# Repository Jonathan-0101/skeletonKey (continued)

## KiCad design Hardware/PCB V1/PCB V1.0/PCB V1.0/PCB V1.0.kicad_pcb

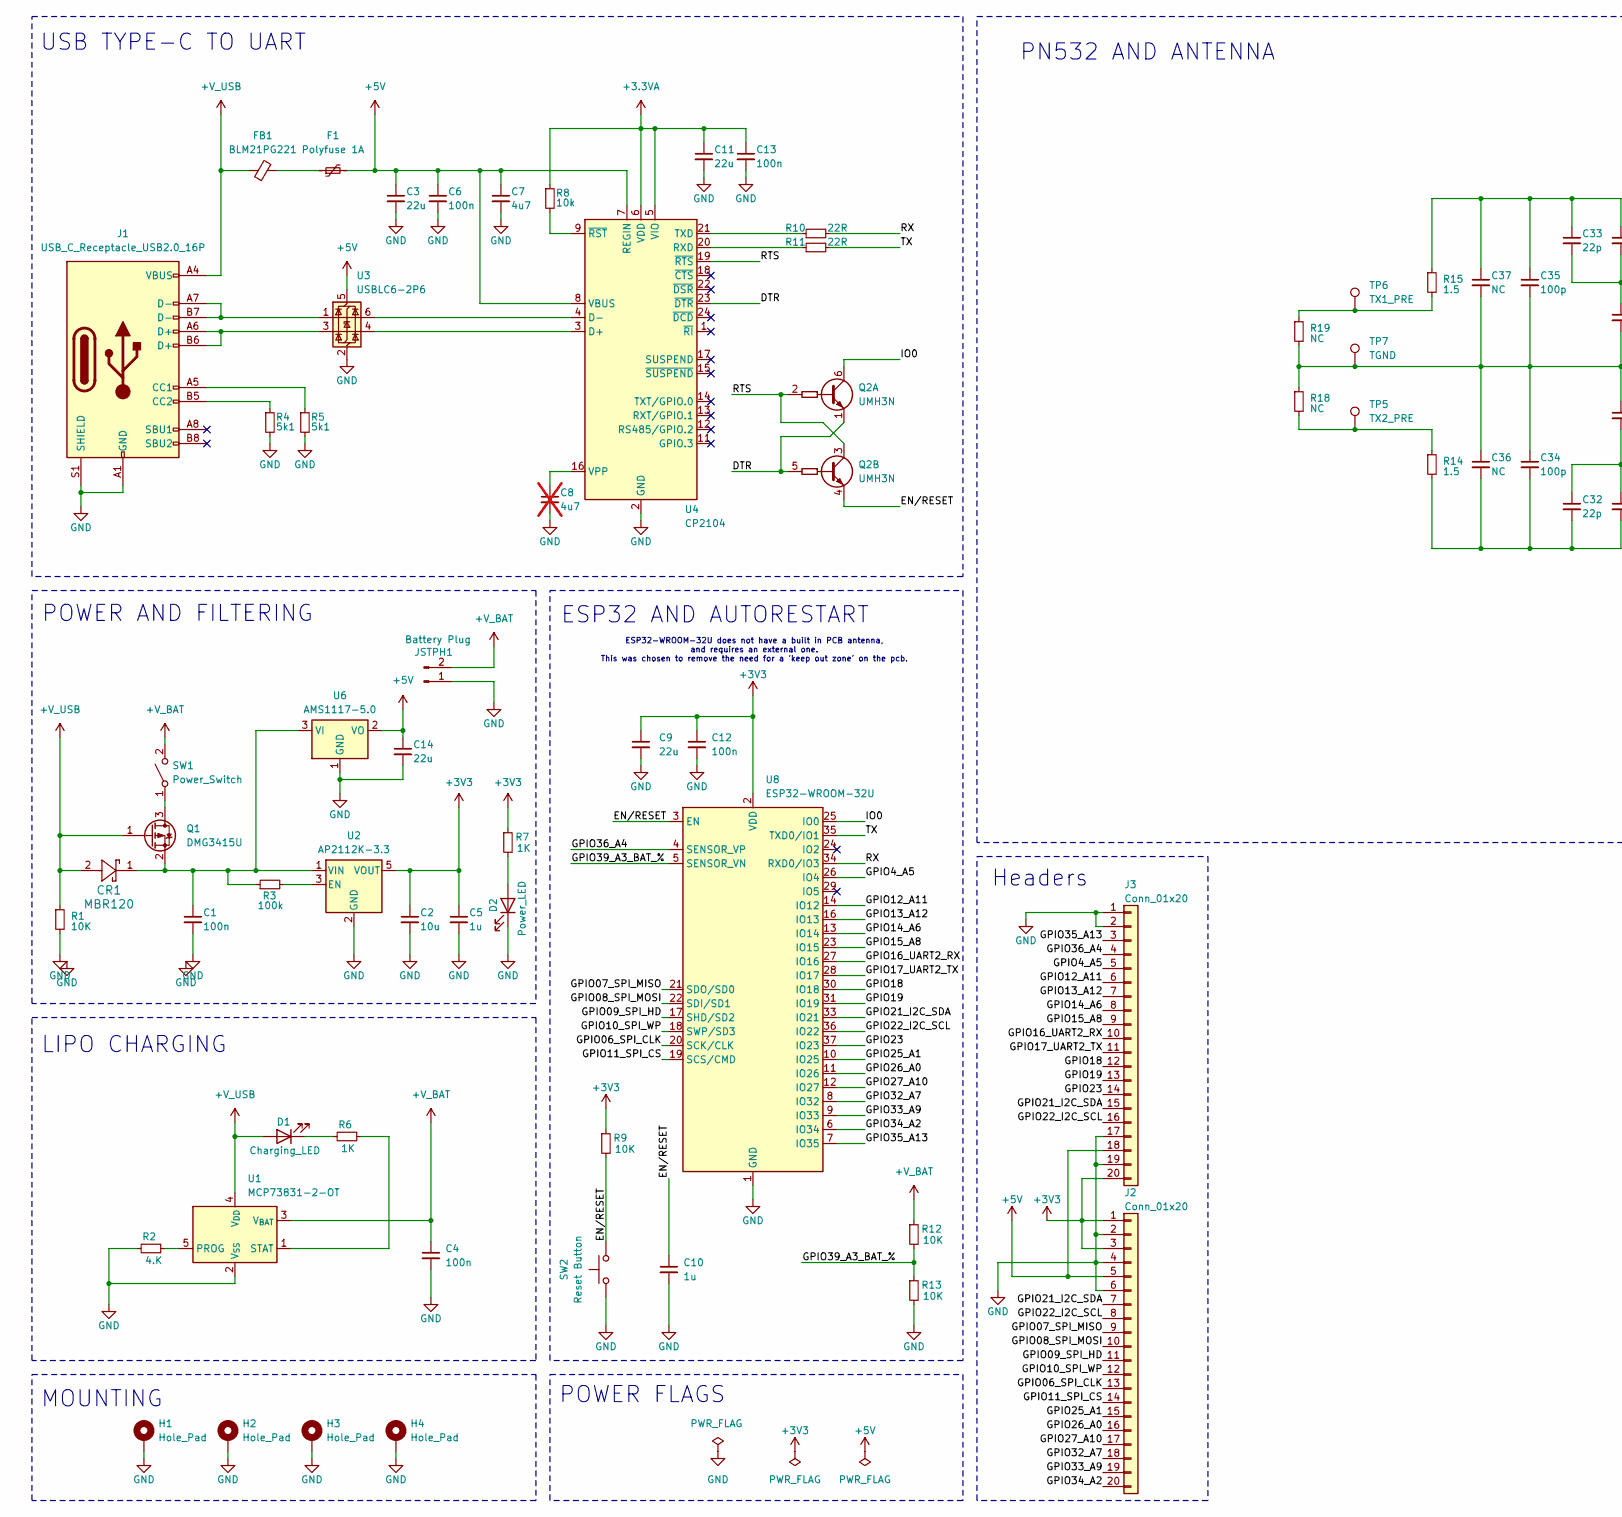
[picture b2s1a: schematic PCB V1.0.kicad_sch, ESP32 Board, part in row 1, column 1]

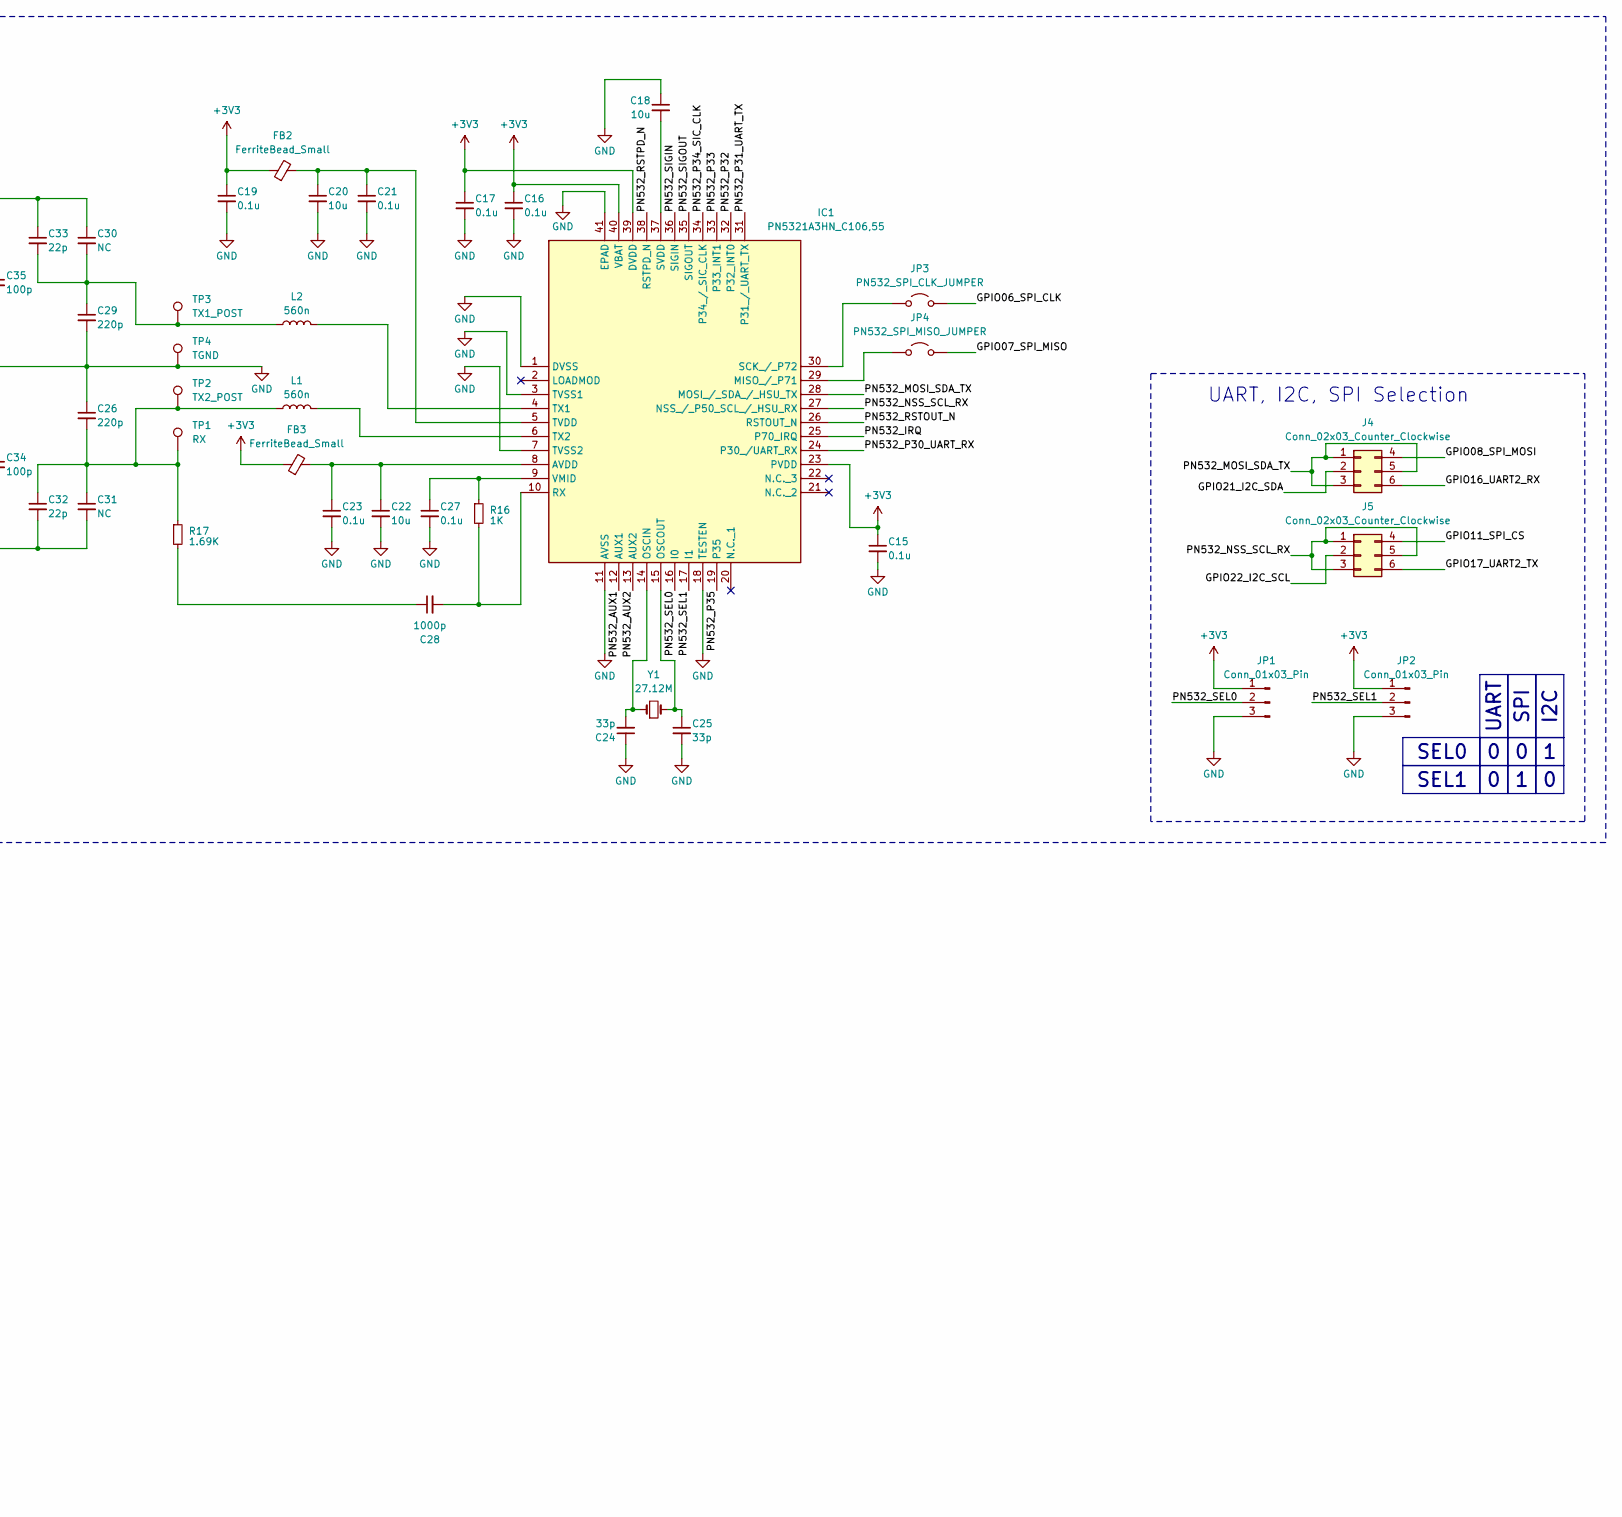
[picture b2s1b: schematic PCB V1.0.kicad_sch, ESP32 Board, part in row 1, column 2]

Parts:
C1, C6, C13: 100n; C_0805_2012Metric_Pad1.18x1.45mm_HandSolder
C2: 10u; C_0805_2012Metric_Pad1.18x1.45mm_HandSolder
C3, C9, C11: 22u; C_0805_2012Metric_Pad1.18x1.45mm_HandSolder
C4, C12: 100n; C_0402_1005Metric_Pad0.74x0.62mm_HandSolder
C5: 1u; C_0805_2012Metric_Pad1.18x1.45mm_HandSolder
C7: 4u7; C_0805_2012Metric_Pad1.18x1.45mm_HandSolder
C8: 4u7; C_0805_2012Metric_Pad1.18x1.45mm_HandSolder; not fitted
C10: 1u; C_0402_1005Metric_Pad0.74x0.62mm_HandSolder
C14: 22u; C_Axial_L3.8mm_D2.6mm_P10.00mm_Horizontal
C15, C16, C17, C19, C21, C23, C27: 0.1u; C_Axial_L3.8mm_D2.6mm_P10.00mm_Horizontal
C18, C20, C22: 10u; C_Axial_L3.8mm_D2.6mm_P10.00mm_Horizontal
C24, C25: 33p; C_Axial_L3.8mm_D2.6mm_P10.00mm_Horizontal
C26, C29: 220p; C_Axial_L3.8mm_D2.6mm_P10.00mm_Horizontal
C28: 1000p; C_Axial_L3.8mm_D2.6mm_P10.00mm_Horizontal
C30, C31, C36, C37: NC; C_Axial_L3.8mm_D2.6mm_P10.00mm_Horizontal
C32, C33: 22p; C_Axial_L3.8mm_D2.6mm_P10.00mm_Horizontal
C34, C35: 100p; C_Axial_L3.8mm_D2.6mm_P10.00mm_Horizontal
CR1: MBR120; SDO_SOD-123FL498_OSI
D1: Charging_LED; LED_0603_1608Metric_Pad1.05x0.95mm_HandSolder
D2: Power_LED; LED_0603_1608Metric_Pad1.05x0.95mm_HandSolder
F1: Polyfuse 1A; Fuse_1206_3216Metric_Pad1.42x1.75mm_HandSolder
FB1: BLM21PG221; L_0603_1608Metric_Pad1.05x0.95mm_HandSolder
FB2, FB3: FerriteBead_Small; BEADC2012X145N
H1, H2, H3, H4: Hole_Pad; MountingHole_2.2mm_M2_Pad_Via
IC1: PN5321A3HN_C106,55; QFN50P600X600X100-41N-D; Mouser Part Number 771-PN5321A3HNC10
J1: USB_C_Receptacle_USB2.0_16P; USB_C_Receptacle_HRO_TYPE-C-31-M-12
J2, J3: Conn_01x20; PinSocket_1x20_P2.54mm_Vertical
J4, J5: Conn_02x03_Counter_Clockwise; PinHeader_2x03_P2.54mm_Vertical
JP1, JP2: Conn_01x03_Pin; PinHeader_1x03_P2.54mm_Vertical
JP3: PN532_SPI_CLK_JUMPER; TestPoint_2Pads_Pitch5.08mm_Drill1.3mm
JP4: PN532_SPI_MISO_JUMPER; TestPoint_2Pads_Pitch5.08mm_Drill1.3mm
JSTPH1: Battery Plug; JST_PH_S2B-PH-K_1x02_P2.00mm_Horizontal
L1, L2: 560n; L_Axial_L5.3mm_D2.2mm_P10.16mm_Horizontal_Vishay_IM-1
Q1: DMG3415U; SOT95P240X105-3N
Q2: UMH3N; SOT-363_SC-70-6
R1, R9, R12, R13: 10K; R_0402_1005Metric_Pad0.72x0.64mm_HandSolder
R2: 4.K; R_0402_1005Metric_Pad0.72x0.64mm_HandSolder
R3: 100k; R_0402_1005Metric_Pad0.72x0.64mm_HandSolder
R4, R5: 5k1; R_0402_1005Metric_Pad0.72x0.64mm_HandSolder
R6, R7: 1K; R_0402_1005Metric_Pad0.72x0.64mm_HandSolder
R8: 10k; R_0402_1005Metric_Pad0.72x0.64mm_HandSolder
R10, R11: 22R; R_0402_1005Metric_Pad0.72x0.64mm_HandSolder
R14, R15: 1.5; R_Axial_DIN0207_L6.3mm_D2.5mm_P10.16mm_Horizontal
R16: 1K; R_Axial_DIN0207_L6.3mm_D2.5mm_P10.16mm_Horizontal
R17: 1.69K; R_Axial_DIN0207_L6.3mm_D2.5mm_P10.16mm_Horizontal
R18, R19: NC; R_Axial_DIN0207_L6.3mm_D2.5mm_P10.16mm_Horizontal
SW1: Power_Switch; SW_DIP_SPSTx01_Slide_9.78x4.72mm_W7.62mm_P2.54mm
SW2: Reset Button; SW_Push_SPST_NO_Alps_SKRK
TP1: RX; TestPoint_Pad_D1.5mm
TP2: TX2_POST; TestPoint_Pad_D1.5mm
TP3: TX1_POST; TestPoint_Pad_D1.5mm
TP4, TP7: TGND; TestPoint_Pad_D1.5mm
TP5: TX2_PRE; TestPoint_Pad_D1.5mm
TP6: TX1_PRE; TestPoint_Pad_D1.5mm
U1: MCP73831-2-OT; SOT-23-5
U2: AP2112K-3.3; SOT-23-5
U3: USBLC6-2P6; SOT-666
U4: CP2104; QFN-24-1EP_4x4mm_P0.5mm_EP2.6x2.6mm
U6: AMS1117-5.0; SOT-223-3_TabPin2
U8: ESP32-WROOM-32U
Y1: 27.12M; XTAL_7M-27.120MAAJ-T

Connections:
+3.3VA: C11.1, C13.1, R8.1, U4.5 (VIO), U4.6 (VDD)
+3V3: C2.1, C5.1, C9.1, C12.1, C15.1, C16.1, C17.1, C19.1, FB2.1, FB3.1, IC1.23 (PVDD), IC1.39 (DVDD), IC1.40 (VBAT), J2.1, J2.3, J3.20, JP1.1, JP2.1, R7.1, R9.1, U2.5 (VOUT), U8.2 (VDD)
+5V: C3.1, C6.1, C7.1, C14.1, F1.2, J2.5, J3.18, U3.5 (VBUS), U4.7 (REGIN), U4.8 (VBUS), U6.2 (VO)
+V_BAT: C4.1, JSTPH1.2, R12.1, SW1.2 (B), U1.3 (V_{BAT})
+V_USB: CR1.2, D1.2 (A), FB1.1, J1.A4 (VBUS), J1.A9 (VBUS), J1.B4 (VBUS), J1.B9 (VBUS), Q1.1 (G), R1.1, U1.4 (V_{DD})
/DTR: Q2.1 (E1), Q2.5 (B2), U4.23 (~DTR)
/EN/RESET: C10.1, Q2.4 (E2), R9.2, SW2.2, U8.3 (EN)
/GPIO4_A5: J3.5, U8.26 (IO4)
/GPIO06_SPI_CLK: J2.13, JP3.2 (B), U8.20 (SCK/CLK)
/GPIO07_SPI_MISO: J2.9, JP4.2 (B), U8.21 (SDO/SD0)
/GPIO08_SPI_MOSI: J2.10, J4.4, U8.22 (SDI/SD1)
/GPIO09_SPI_HD: J2.11, U8.17 (SHD/SD2)
/GPIO10_SPI_WP: J2.12, U8.18 (SWP/SD3)
/GPIO11_SPI_CS: J2.14, J5.4, U8.19 (SCS/CMD)
/GPIO12_A11: J3.6, U8.14 (IO12)
/GPIO13_A12: J3.7, U8.16 (IO13)
/GPIO14_A6: J3.8, U8.13 (IO14)
/GPIO15_A8: J3.9, U8.23 (IO15)
/GPIO16_UART2_RX: J3.10, J4.6, U8.27 (IO16)
/GPIO17_UART2_TX: J3.11, J5.6, U8.28 (IO17)
/GPIO18: J3.12, U8.30 (IO18)
/GPIO19: J3.13, U8.31 (IO19)
/GPIO21_I2C_SDA: J2.7, J3.15, J4.2, U8.33 (IO21)
/GPIO22_I2C_SCL: J2.8, J3.16, J5.2, U8.36 (IO22)
/GPIO23: J3.14, U8.37 (IO23)
/GPIO25_A1: J2.15, U8.10 (IO25)
/GPIO26_A0: J2.16, U8.11 (IO26)
/GPIO27_A10: J2.17, U8.12 (IO27)
/GPIO32_A7: J2.18, U8.8 (IO32)
/GPIO33_A9: J2.19, U8.9 (IO33)
/GPIO34_A2: J2.20, U8.6 (IO34)
/GPIO35_A13: J3.3, U8.7 (IO35)
/GPIO36_A4: J3.4, U8.4 (SENSOR_VP)
/GPIO39_A3_BAT_%: R12.2, R13.1, U8.5 (SENSOR_VN)
/IO0: Q2.6 (C1), U8.25 (IO0)
/PN532_AUX1: IC1.12 (AUX1)
/PN532_AUX2: IC1.13 (AUX2)
/PN532_IRQ: IC1.25 (P70_IRQ)
/PN532_MOSI_SDA_TX: IC1.28 (MOSI_/_SDA_/_HSU_TX), J4.1, J4.3, J4.5
/PN532_NSS_SCL_RX: IC1.27 (NSS_/_P50_SCL_/_HSU_RX), J5.1, J5.3, J5.5
/PN532_P30_UART_RX: IC1.24 (P30_/UART_RX)
/PN532_P31_UART_TX: IC1.31 (P31_/_UART_TX)
/PN532_P32: IC1.32 (P32_INT0)
/PN532_P33: IC1.33 (P33_INT1)
/PN532_P34_SIC_CLK: IC1.34 (P34_/_SIC_CLK)
/PN532_P35: IC1.19 (P35)
/PN532_RSTOUT_N: IC1.26 (RSTOUT_N)
/PN532_RSTPD_N: IC1.38 (RSTPD_N)
/PN532_SEL0: IC1.16 (I0), JP1.2
/PN532_SEL1: IC1.17 (I1), JP2.2
/PN532_SIGIN: IC1.36 (SIGIN)
/PN532_SIGOUT: IC1.35 (SIGOUT)
/RTS: Q2.2 (B1), Q2.3 (C2), U4.19 (~RTS)
/RX: R10.2, U8.34 (RXD0/IO3)
/TX: R11.2, U8.35 (TXD0/IO1)
GND: C1.2, C2.2, C3.2, C4.2, C5.2, C6.2, C7.2, C8.2, C9.2, C10.2, C11.2, C12.2, C13.2, C14.2, C15.2, C16.2, C17.2, C18.1, C19.2, C20.2, C21.2, C22.2, C23.2, C24.1, C25.2, C26.1, C27.2, C29.2, C34.1, C35.2, C36.1, C37.2, D2.1 (K), H1.1, H2.1, H3.1, H4.1, IC1.1 (DVSS), IC1.3 (TVSS1), IC1.7 (TVSS2), IC1.11 (AVSS), IC1.18 (TESTEN), IC1.41 (EPAD), J1.A1 (GND), J1.A12 (GND), J1.B1 (GND), J1.B12 (GND), J1.S1 (SHIELD), J2.2, J2.4, J2.6, J3.1, J3.2, J3.17, J3.19, JP1.3, JP2.3, JSTPH1.1, R1.2, R2.2, R4.2, R5.2, R13.2, R18.1, R19.2, SW2.1, TP4.1, TP7.1, U1.2 (V_{SS}), U2.2 (GND), U3.2 (GND), U4.2 (GND), U4.25 (GND), U6.1 (GND), U8.1 (GND), U8.15 (GND), U8.38 (GND), U8.39 (GND)
unnamed: C26.2, C31.1, C32.1, L1.1, R17.1, TP1.1, TP2.1
unnamed: C28.1, R17.2
unnamed: C29.1, C30.2, C33.2, L2.1, TP3.1
unnamed: C30.1, C33.1, C35.1, C37.1, R15.1
unnamed: C31.2, C32.2, C34.2, C36.2, R14.2
unnamed: D1.1 (K), R6.2
unnamed: D2.2 (A), R7.2
unnamed: F1.1, FB1.2
unnamed: C22.1, C23.1, FB3.2, IC1.8 (AVDD)
unnamed: IC1.29 (MISO_/_P71), JP4.1 (A)
unnamed: C24.2, IC1.14 (OSCIN), Y1.1
unnamed: C25.1, IC1.15 (OSCOUT), Y1.2
unnamed: C28.2, IC1.10 (RX), R16.2
unnamed: IC1.30 (SCK_/_P72), JP3.1 (A)
unnamed: C18.2, IC1.37 (SVDD)
unnamed: C20.1, C21.1, FB2.2, IC1.5 (TVDD)
unnamed: IC1.4 (TX1), L2.2
unnamed: IC1.6 (TX2), L1.2
unnamed: C27.1, IC1.9 (VMID), R16.1
unnamed: J1.A5 (CC1), R5.1
unnamed: J1.B5 (CC2), R4.1
unnamed: J1.A6 (D+), J1.B6 (D+), U3.3 (I/O2)
unnamed: J1.A7 (D-), J1.B7 (D-), U3.1 (I/O1)
unnamed: Q1.3 (D), SW1.1 (A)
unnamed: C1.1, CR1.1, Q1.2 (S), R3.1, U2.1 (VIN), U6.3 (VI)
unnamed: R14.1, R18.2, TP5.1
unnamed: R15.2, R19.1, TP6.1
unnamed: R2.1, U1.5 (PROG)
unnamed: R6.1, U1.1 (STAT)
unnamed: R3.2, U2.3 (EN)
unnamed: U3.4 (I/O2), U4.3 (D+)
unnamed: U3.6 (I/O1), U4.4 (D-)
unnamed: R11.1, U4.20 (RXD)
unnamed: R10.1, U4.21 (TXD)
unnamed: C8.1, U4.16 (VPP)
unnamed: R8.2, U4.9 (~RST)

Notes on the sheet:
SPI
I2C
SEL0
UART
SEL1
PN532 AND ANTENNA
LIPO CHARGING
Headers
ESP32-WROOM-32U does not have a built in PCB antenna, and requires an external one. This was chosen to remove the need for a 'keep out zone' on the pcb.
USB TYPE-C TO UART
ESP32 AND AUTORESTART
UART, I2C, SPI Selection
POWER FLAGS
MOUNTING
POWER AND FILTERING

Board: 2 copper layers, 97 parts (0 on the bottom side), 78 nets, no tracks yet.

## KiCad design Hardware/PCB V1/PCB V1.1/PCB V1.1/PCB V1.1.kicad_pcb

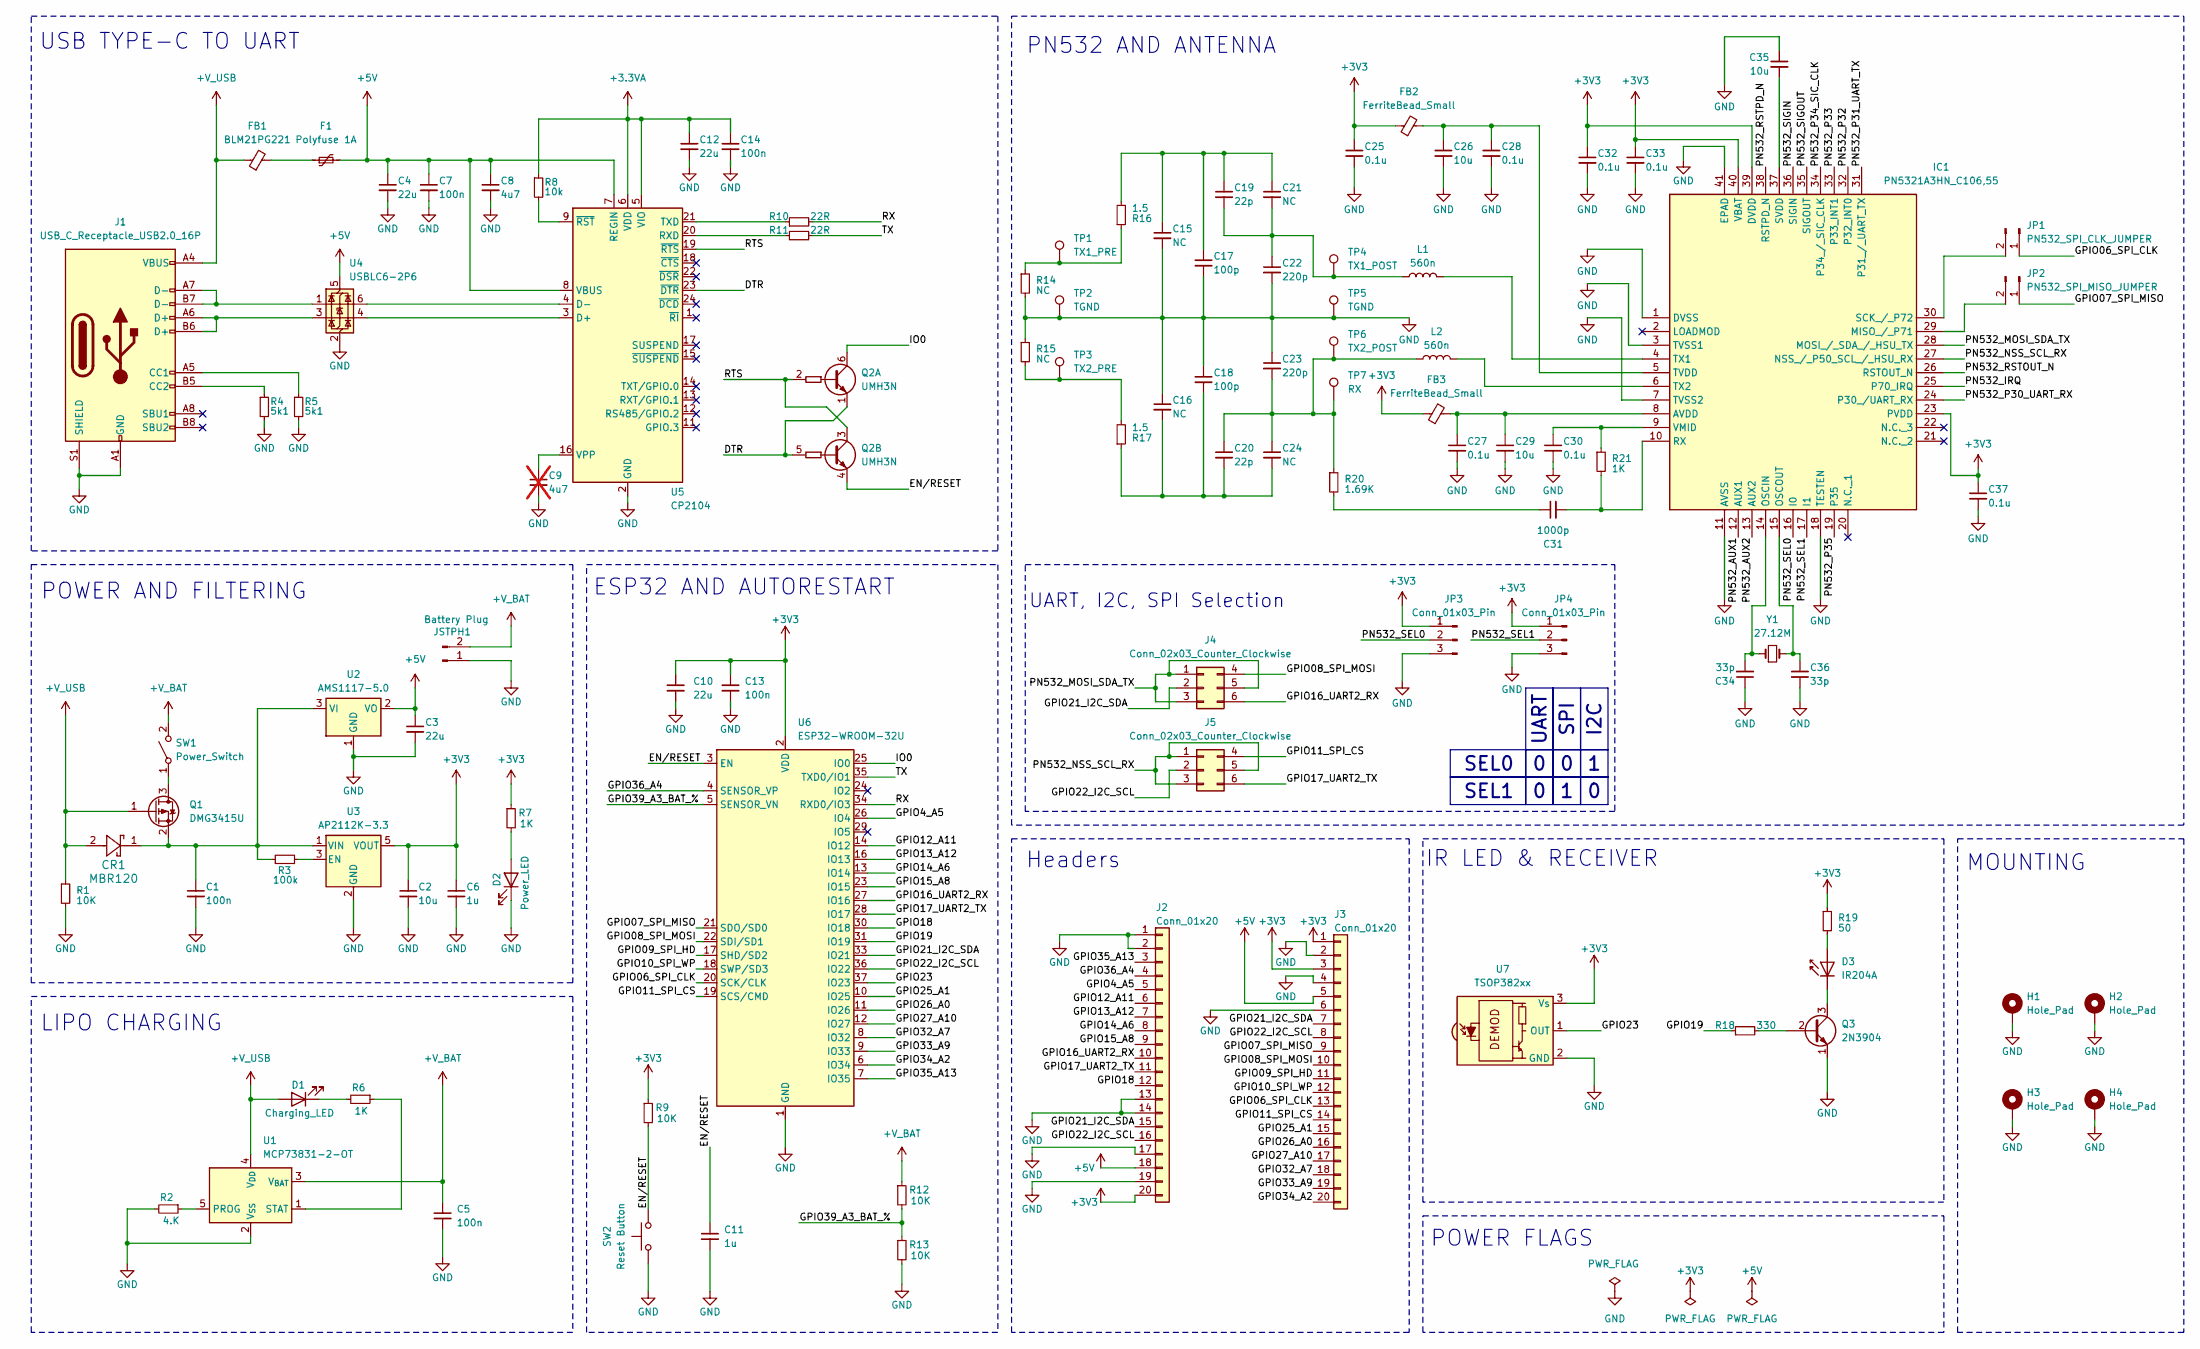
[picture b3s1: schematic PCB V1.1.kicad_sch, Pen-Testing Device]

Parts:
C1, C7, C14: 100n; C_0805_2012Metric_Pad1.18x1.45mm_HandSolder
C2: 10u; C_0805_2012Metric_Pad1.18x1.45mm_HandSolder
C3, C4, C10, C12: 22u; C_0805_2012Metric_Pad1.18x1.45mm_HandSolder
C5, C13: 100n; C_0402_1005Metric_Pad0.74x0.62mm_HandSolder
C6: 1u; C_0805_2012Metric_Pad1.18x1.45mm_HandSolder
C8: 4u7; C_0805_2012Metric_Pad1.18x1.45mm_HandSolder
C9: 4u7; C_0805_2012Metric_Pad1.18x1.45mm_HandSolder; not fitted
C11: 1u; C_0402_1005Metric_Pad0.74x0.62mm_HandSolder
C15, C16, C21, C24: NC; C_Disc_D7.5mm_W2.5mm_P5.00mm
C17, C18: 100p; C_Disc_D7.5mm_W2.5mm_P5.00mm
C19, C20: 22p; C_Disc_D7.5mm_W2.5mm_P5.00mm
C22, C23: 220p; C_Disc_D7.5mm_W2.5mm_P5.00mm
C25, C27, C28, C30, C32, C33, C37: 0.1u; C_Disc_D7.5mm_W2.5mm_P5.00mm
C26, C29, C35: 10u; C_Disc_D7.5mm_W2.5mm_P5.00mm
C31: 1000p; C_Disc_D7.5mm_W2.5mm_P5.00mm
C34, C36: 33p; C_Disc_D7.5mm_W2.5mm_P5.00mm
CR1: MBR120; SDO_SOD-123FL498_OSI
D1: Charging_LED; LED_0603_1608Metric_Pad1.05x0.95mm_HandSolder
D2: Power_LED; LED_0603_1608Metric_Pad1.05x0.95mm_HandSolder
D3: IR204A; LED_D3.0mm_IRBlack
F1: Polyfuse 1A; Fuse_1206_3216Metric_Pad1.42x1.75mm_HandSolder
FB1: BLM21PG221; L_0603_1608Metric_Pad1.05x0.95mm_HandSolder
FB2, FB3: FerriteBead_Small; BEADC2012X145N
H1, H2, H3, H4: Hole_Pad; MountingHole_2.2mm_M2_Pad_Via
IC1: PN5321A3HN_C106,55; QFN50P600X600X100-41N-D; Mouser Part Number 771-PN5321A3HNC10
J1: USB_C_Receptacle_USB2.0_16P; USB_C_Receptacle_HRO_TYPE-C-31-M-12
J2, J3: Conn_01x20; PinSocket_1x20_P2.54mm_Vertical
J4, J5: Conn_02x03_Counter_Clockwise; PinHeader_2x03_P2.54mm_Vertical
JP1: PN532_SPI_CLK_JUMPER; PinHeader_2x01_P2.54mm_Vertical
JP2: PN532_SPI_MISO_JUMPER; PinHeader_2x01_P2.54mm_Vertical
JP3, JP4: Conn_01x03_Pin; PinHeader_1x03_P2.54mm_Vertical
JSTPH1: Battery Plug; JST_PH_S2B-PH-K_1x02_P2.00mm_Horizontal
L1, L2: 560n; L_Axial_L5.3mm_D2.2mm_P10.16mm_Horizontal_Vishay_IM-1
Q1: DMG3415U; SOT95P240X105-3N
Q2: UMH3N; SOT-363_SC-70-6
Q3: 2N3904; TO-92_Inline
R1, R9, R12, R13: 10K; R_0402_1005Metric_Pad0.72x0.64mm_HandSolder
R2: 4.K; R_0402_1005Metric_Pad0.72x0.64mm_HandSolder
R3: 100k; R_0402_1005Metric_Pad0.72x0.64mm_HandSolder
R4, R5: 5k1; R_0402_1005Metric_Pad0.72x0.64mm_HandSolder
R6, R7: 1K; R_0402_1005Metric_Pad0.72x0.64mm_HandSolder
R8: 10k; R_0402_1005Metric_Pad0.72x0.64mm_HandSolder
R10, R11: 22R; R_0402_1005Metric_Pad0.72x0.64mm_HandSolder
R14, R15: NC; R_0201_0603Metric_Pad0.64x0.40mm_HandSolder
R16, R17: 1.5; R_Axial_DIN0207_L6.3mm_D2.5mm_P10.16mm_Horizontal
R18: 330; R_Axial_DIN0207_L6.3mm_D2.5mm_P10.16mm_Horizontal
R19: 50; R_Axial_DIN0207_L6.3mm_D2.5mm_P10.16mm_Horizontal
R20: 1.69K; R_Axial_DIN0207_L6.3mm_D2.5mm_P10.16mm_Horizontal
R21: 1K; R_Axial_DIN0207_L6.3mm_D2.5mm_P10.16mm_Horizontal
SW1: Power_Switch; SW_DIP_SPSTx01_Slide_9.78x4.72mm_W7.62mm_P2.54mm
SW2: Reset Button; SW_Push_SPST_NO_Alps_SKRK
TP1: TX1_PRE; TestPoint_Pad_D1.5mm
TP2, TP5: TGND; TestPoint_Pad_D1.5mm
TP3: TX2_PRE; TestPoint_Pad_D1.5mm
TP4: TX1_POST; TestPoint_Pad_D1.5mm
TP6: TX2_POST; TestPoint_Pad_D1.5mm
TP7: RX; TestPoint_Pad_D1.5mm
U1: MCP73831-2-OT; SOT-23-5
U2: AMS1117-5.0; SOT-223-3_TabPin2
U3: AP2112K-3.3; SOT-23-5
U4: USBLC6-2P6; SOT-666
U5: CP2104; QFN-24-1EP_4x4mm_P0.5mm_EP2.6x2.6mm
U6: ESP32-WROOM-32U
U7: TSOP382xx; Vishay_MINICAST-3Pin
Y1: 27.12M; XTAL_7M-27.120MAAJ-T

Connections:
+3.3VA: C12.1, C14.1, R8.1, U5.5 (VIO), U5.6 (VDD)
+V_BAT: C5.1, JSTPH1.2, R12.1, SW1.2 (B), U1.3 (V_{BAT})
+V_USB: CR1.2, D1.2 (A), FB1.1, J1.A4 (VBUS), J1.A9 (VBUS), J1.B4 (VBUS), J1.B9 (VBUS), Q1.1 (G), R1.1, U1.4 (V_{DD})
/DTR: Q2.1 (E1), Q2.5 (B2), U5.23 (~DTR)
/EN/RESET: C11.1, Q2.4 (E2), R9.2, SW2.2, U6.3 (EN)
/GPIO4_A5: J2.5, U6.26 (IO4)
/GPIO06_SPI_CLK: J3.13, JP1.1, U6.20 (SCK/CLK)
/GPIO07_SPI_MISO: J3.9, JP2.1, U6.21 (SDO/SD0)
/GPIO08_SPI_MOSI: J3.10, J4.4, U6.22 (SDI/SD1)
/GPIO09_SPI_HD: J3.11, U6.17 (SHD/SD2)
/GPIO10_SPI_WP: J3.12, U6.18 (SWP/SD3)
/GPIO11_SPI_CS: J3.14, J5.4, U6.19 (SCS/CMD)
/GPIO12_A11: J2.6, U6.14 (IO12)
/GPIO13_A12: J2.7, U6.16 (IO13)
/GPIO14_A6: J2.8, U6.13 (IO14)
/GPIO15_A8: J2.9, U6.23 (IO15)
/GPIO16_UART2_RX: J2.10, J4.6, U6.27 (IO16)
/GPIO17_UART2_TX: J2.11, J5.6, U6.28 (IO17)
/GPIO18: J2.12, U6.30 (IO18)
/GPIO19: R18.1, U6.31 (IO19)
/GPIO21_I2C_SDA: J2.15, J3.7, J4.2, U6.33 (IO21)
/GPIO22_I2C_SCL: J2.16, J3.8, J5.2, U6.36 (IO22)
/GPIO23: U6.37 (IO23), U7.1 (OUT)
/GPIO25_A1: J3.15, U6.10 (IO25)
/GPIO26_A0: J3.16, U6.11 (IO26)
/GPIO27_A10: J3.17, U6.12 (IO27)
/GPIO32_A7: J3.18, U6.8 (IO32)
/GPIO33_A9: J3.19, U6.9 (IO33)
/GPIO34_A2: J3.20, U6.6 (IO34)
/GPIO35_A13: J2.3, U6.7 (IO35)
/GPIO36_A4: J2.4, U6.4 (SENSOR_VP)
/GPIO39_A3_BAT_%: R12.2, R13.1, U6.5 (SENSOR_VN)
/IO0: Q2.6 (C1), U6.25 (IO0)
/PN532_AUX1: IC1.12 (AUX1)
/PN532_AUX2: IC1.13 (AUX2)
/PN532_IRQ: IC1.25 (P70_IRQ)
/PN532_MOSI_SDA_TX: IC1.28 (MOSI_/_SDA_/_HSU_TX), J4.1, J4.3, J4.5
/PN532_NSS_SCL_RX: IC1.27 (NSS_/_P50_SCL_/_HSU_RX), J5.1, J5.3, J5.5
/PN532_P30_UART_RX: IC1.24 (P30_/UART_RX)
/PN532_P31_UART_TX: IC1.31 (P31_/_UART_TX)
/PN532_P32: IC1.32 (P32_INT0)
/PN532_P33: IC1.33 (P33_INT1)
/PN532_P34_SIC_CLK: IC1.34 (P34_/_SIC_CLK)
/PN532_P35: IC1.19 (P35)
/PN532_RSTOUT_N: IC1.26 (RSTOUT_N)
/PN532_RSTPD_N: IC1.38 (RSTPD_N)
/PN532_SEL0: IC1.16 (I0), JP3.2
/PN532_SEL1: IC1.17 (I1), JP4.2
/PN532_SIGIN: IC1.36 (SIGIN)
/PN532_SIGOUT: IC1.35 (SIGOUT)
/RTS: Q2.2 (B1), Q2.3 (C2), U5.19 (~RTS)
/RX: R10.2, U6.34 (RXD0/IO3)
/TX: R11.2, U6.35 (TXD0/IO1)
GND: C1.2, C2.2, C3.2, C4.2, C5.2, C6.2, C7.2, C8.2, C9.2, C10.2, C11.2, C12.2, C13.2, C14.2, C15.2, C16.1, C17.2, C18.1, C22.2, C23.1, C25.2, C26.2, C27.2, C28.2, C29.2, C30.2, C32.2, C33.2, C34.1, C35.1, C36.2, C37.2, D2.1 (K), H1.1, H2.1, H3.1, H4.1, IC1.1 (DVSS), IC1.3 (TVSS1), IC1.7 (TVSS2), IC1.11 (AVSS), IC1.18 (TESTEN), IC1.41 (EPAD), J1.A1 (GND), J1.A12 (GND), J1.B1 (GND), J1.B12 (GND), J1.S1 (SHIELD), J2.1, J2.2, J2.13, J2.14, J2.17, J2.19, J3.2, J3.4, J3.6, JP3.3, JP4.3, JSTPH1.1, Q3.1 (E), R1.2, R2.2, R4.2, R5.2, R13.2, R14.2, R15.1, SW2.1, TP2.1, TP5.1, U1.2 (V_{SS}), U2.1 (GND), U3.2 (GND), U4.2 (GND), U5.2 (GND), U5.25 (GND), U6.1 (GND), U6.15 (GND), U6.38 (GND), U6.39 (GND), U7.2 (GND); also elsewhere on the board
unnamed: C15.1, C17.1, C19.1, C21.1, R16.2
unnamed: C16.2, C18.2, C20.2, C24.2, R17.1
unnamed: C19.2, C21.2, C22.1, L1.1, TP4.1
unnamed: C20.1, C23.2, C24.1, L2.1, R20.1, TP6.1, TP7.1
unnamed: C31.1, R20.2
unnamed: D1.1 (K), R6.2
unnamed: D2.2 (A), R7.2
unnamed: D3.2 (A), R19.2
unnamed: D3.1 (K), Q3.3 (C)
unnamed: F1.1, FB1.2
unnamed: C27.1, C29.1, FB3.2, IC1.8 (AVDD)
unnamed: IC1.29 (MISO_/_P71), JP2.2
unnamed: C34.2, IC1.14 (OSCIN), Y1.1
unnamed: C36.1, IC1.15 (OSCOUT), Y1.2
unnamed: C31.2, IC1.10 (RX), R21.2
unnamed: IC1.30 (SCK_/_P72), JP1.2
unnamed: C35.2, IC1.37 (SVDD)
unnamed: C26.1, C28.1, FB2.2, IC1.5 (TVDD)
unnamed: IC1.4 (TX1), L1.2
unnamed: IC1.6 (TX2), L2.2
unnamed: C30.1, IC1.9 (VMID), R21.1
unnamed: J1.A5 (CC1), R5.1
unnamed: J1.B5 (CC2), R4.1
unnamed: J1.A6 (D+), J1.B6 (D+), U4.3 (I/O2)
unnamed: J1.A7 (D-), J1.B7 (D-), U4.1 (I/O1)
unnamed: Q1.3 (D), SW1.1 (A)
unnamed: C1.1, CR1.1, Q1.2 (S), R3.1, U2.3 (VI), U3.1 (VIN)
unnamed: Q3.2 (B), R18.2
unnamed: R14.1, R16.1, TP1.1
unnamed: R15.2, R17.2, TP3.1
unnamed: R2.1, U1.5 (PROG)
unnamed: R6.1, U1.1 (STAT)
unnamed: R3.2, U3.3 (EN)
unnamed: U4.4 (I/O2), U5.3 (D+)
unnamed: U4.6 (I/O1), U5.4 (D-)
unnamed: R11.1, U5.20 (RXD)
unnamed: R10.1, U5.21 (TXD)
unnamed: C9.1, U5.16 (VPP)
unnamed: R8.2, U5.9 (~RST)

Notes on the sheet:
I2C
UART
SPI
SEL0
SEL1
LIPO CHARGING
IR LED & RECEIVER
UART, I2C, SPI Selection
Headers
USB TYPE-C TO UART
PN532 AND ANTENNA
ESP32 AND AUTORESTART
POWER FLAGS
MOUNTING
POWER AND FILTERING

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
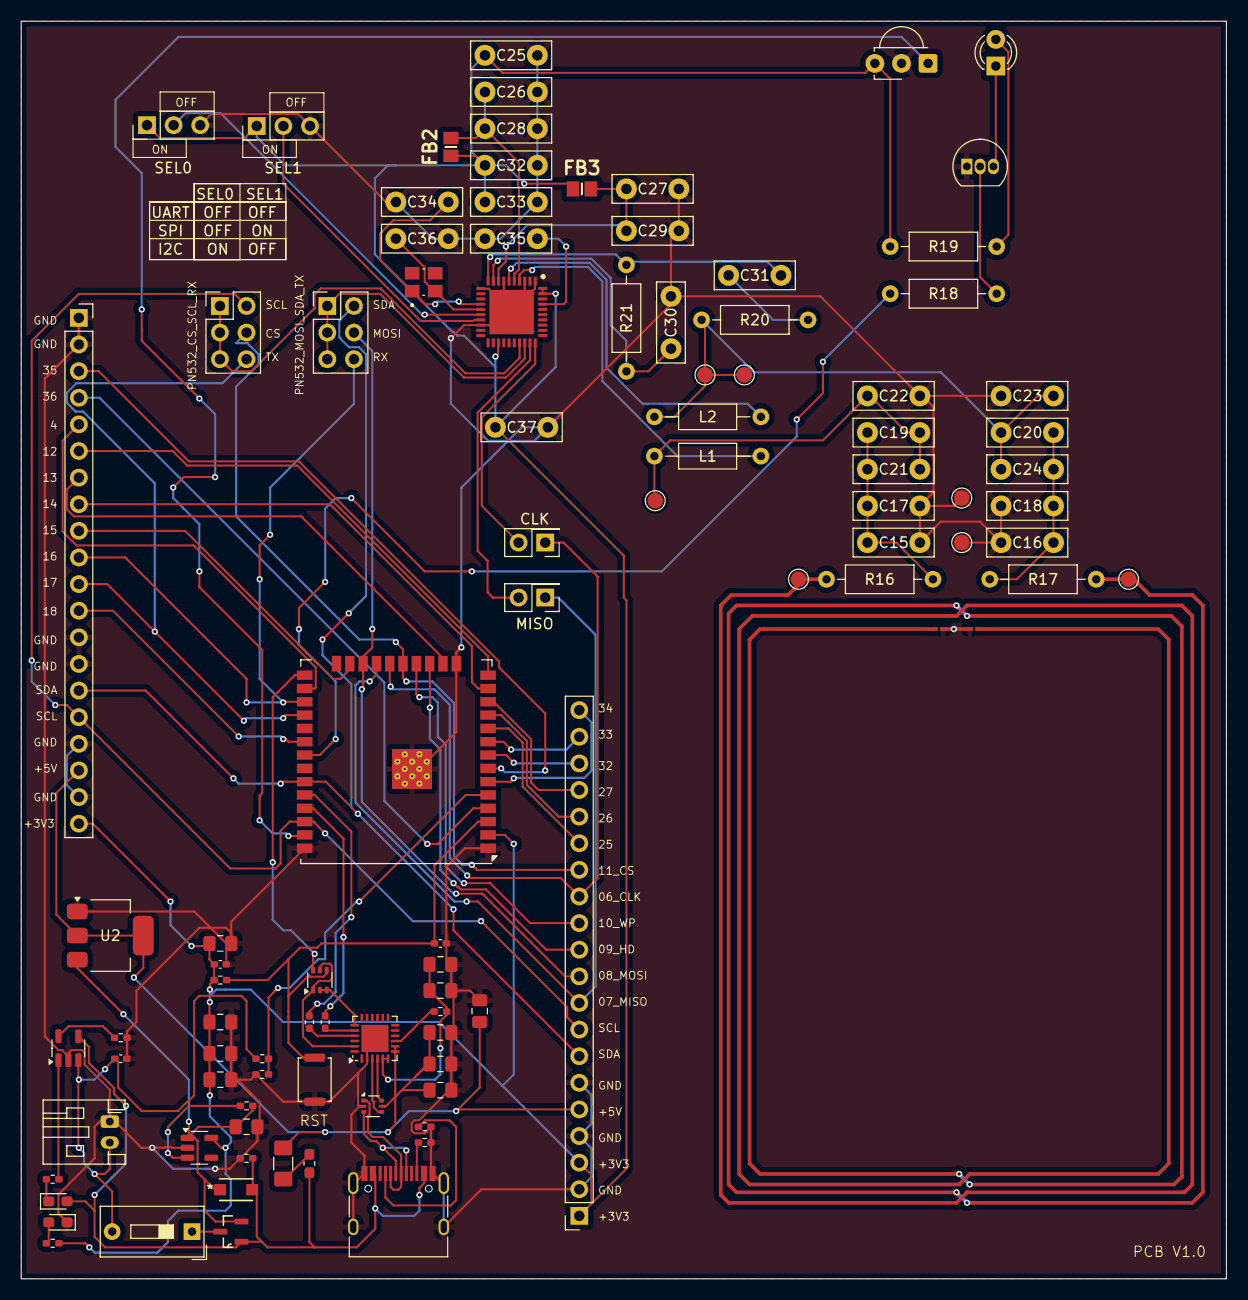
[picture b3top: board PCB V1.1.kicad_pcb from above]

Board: 2 copper layers, 115.0 x 120.0 mm, 99 parts (0 on the bottom side), 81 nets.

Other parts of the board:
C8#2: 4u7; C_0805_2012Metric_Pad1.18x1.45mm_HandSolder

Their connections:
GND: C8#2.2; also elsewhere on the board

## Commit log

2025-02-11 Menu test code
2025-02-11 Update gitignore
2025-02-25 Added WiFi Beacon Rick Roll Spam
2025-02-25 WiFi fix
2025-02-26 Deauthentication attack added
2025-03-01 Update WiFi tools
2025-03-02 Location moved
2025-03-02 Added WiFi_Client_Finder
2025-03-02 Removed menu_test
2025-03-03 Added client identification
2025-03-03 Handshake capture working
2025-03-04 Doxygen Comments added to WiFiTools.h
2025-03-04 Clean gh-pages branch
2025-03-04 Added Doxygen auto deployment
2025-03-04 Added doxyfile
2025-03-04 Deploying to gh-pages from @ Jonathan-0101/PenTestingDevice@9b835ae439a8a076c469b3e125c4329d3b172048 🚀
2025-03-05 Update doxyfile
2025-03-05 Deploying to gh-pages from @ Jonathan-0101/PenTestingDevice@25d78661cd32d092337b3c88ce15a98935077e97 🚀
2025-03-05 Deploying to gh-pages from @ Jonathan-0101/PenTestingDevice@27a840fbca0b6b3d2f9da4a3c431f38b2ffa417c 🚀
2025-03-05 Deploying to gh-pages from @ Jonathan-0101/PenTestingDevice@fce74c56ba4e66c465473a5e164fe303f39656ea 🚀
2025-03-05 Add status badge to readme
2025-03-05 Deploying to gh-pages from @ Jonathan-0101/PenTestingDevice@b3fe4fee0658588d52d9da0eaafb632d14fda9f4 🚀
2025-03-05 Change logo
2025-03-05 Deploying to gh-pages from @ Jonathan-0101/PenTestingDevice@d031774ce539a4ac1154097e42c37d0718bd2c9c 🚀
2025-03-05 Adding doxygen customisation
2025-03-05 Deploying to gh-pages from @ Jonathan-0101/PenTestingDevice@9c519b39b7ded5c7c7942e9da1a849dd68b4e4cf 🚀
2025-03-05 Add required files
2025-03-05 Deploying to gh-pages from @ Jonathan-0101/PenTestingDevice@4e8ebd247300c7132a7ff84b1adb6412360ac0c9 🚀
2025-03-05 Deploying to gh-pages from @ Jonathan-0101/PenTestingDevice@b3dbe1ed7572092eec55b46313c8c6e1e15ad02f 🚀
2025-03-05 Update doxygen
2025-03-05 Deploying to gh-pages from @ Jonathan-0101/PenTestingDevice@3dd54b43c25862d19a279b9e8b683f4639d50cf6 🚀
2025-03-05 Begun IR implementation
2025-03-05 Deploying to gh-pages from @ Jonathan-0101/PenTestingDevice@84dca521464bd4821ba9f8425471654963376804 🚀
2025-03-07 IR file parsing and command execution working
2025-03-07 Deploying to gh-pages from @ Jonathan-0101/PenTestingDevice@e48b3b4ecd199f5bb564fb4759e61319f9322d13 🚀
2025-03-07 Cleanup and added doxygen comments to IRTools.h
2025-03-07 Deploying to gh-pages from @ Jonathan-0101/PenTestingDevice@6b4a3f9192a098e683fb4231cc5e1ac53d63565a 🚀
2025-03-07 Deploying to gh-pages from @ Jonathan-0101/PenTestingDevice@4ef8a50929b45646d52d2304057022d416cd9103 🚀
2025-03-07 Added readme.md to IR and WiFi folders
2025-03-07 Deploying to gh-pages from @ Jonathan-0101/PenTestingDevice@96c71f051e52f1c68d914634d708b4c236223ed8 🚀
2025-03-07 Deploying to gh-pages from @ Jonathan-0101/PenTestingDevice@6c5a115e7ff8b6a6882664d8e74bc6f3344895a3 🚀
2025-03-07 Cleanup
2025-03-07 Deploying to gh-pages from @ Jonathan-0101/PenTestingDevice@f34a0df6f92e0a977f8e1333b224a280c3fca73d 🚀
2025-03-07 Added support for aditional protocols
2025-03-07 Deploying to gh-pages from @ Jonathan-0101/PenTestingDevice@fda9c8049d53fafd62bb01ed04530ae30cf1310e 🚀
2025-03-07 Deploying to gh-pages from @ Jonathan-0101/PenTestingDevice@f90168317e90367fff7b72426b3f34a8b3af602b 🚀
2025-03-07 Deploying to gh-pages from @ Jonathan-0101/PenTestingDevice@b44e7eb616579860dd4db90aab21c351d39a1a00 🚀
2025-03-07 Deploying to gh-pages from @ Jonathan-0101/PenTestingDevice@d0158f7a7e9a6bc867b91843e26fd8aecb8867db 🚀
2025-03-07 Fix spacing in doxygen
2025-03-07 Deploying to gh-pages from @ Jonathan-0101/PenTestingDevice@c018e355e0dac7d28a3212cbb91a39cac2fbdc38 🚀
2025-03-07 Deploying to gh-pages from @ Jonathan-0101/PenTestingDevice@c681b9cdcac13f59a220169e83dd9ec94c93db78 🚀
2025-03-07 Changed css
2025-03-07 Deploying to gh-pages from @ Jonathan-0101/PenTestingDevice@75b9b4978f1464f815c7466748cac29fcdc000fc 🚀
2025-03-07 Deploying to gh-pages from @ Jonathan-0101/PenTestingDevice@a6a85e22adfc06f2ddbf34f975db8909214aa6b8 🚀
2025-03-07 Update doxy
2025-03-07 Deploying to gh-pages from @ Jonathan-0101/PenTestingDevice@e32fc16bdfc74b766092d61febc2b624f408529d 🚀
2025-03-07 Deploying to gh-pages from @ Jonathan-0101/PenTestingDevice@a4f1dc393d6cfa66105312fc33bdf25774b2ef3a 🚀
2025-03-07 Deploying to gh-pages from @ Jonathan-0101/PenTestingDevice@32da439b23930bc618b5c36ebfa411e76bd937b4 🚀
2025-03-08 Update README.md
    Fixed typo
2025-03-08 Deploying to gh-pages from @ Jonathan-0101/PenTestingDevice@24784345610c1f95ef4d9592b6463353fd5a58c1 🚀
2025-03-27 Update IR pin assignment
2025-03-27 Update GUI
2025-03-27 Deploying to gh-pages from @ Jonathan-0101/PenTestingDevice@43eba1ad836ff60fc4c5cef10cc33a52b86daae5 🚀
2025-04-14 Added base of SubGHzTools
2025-04-14 Addded SD card to WiFiTools
2025-04-14 Deploying to gh-pages from @ Jonathan-0101/PenTestingDevice@ac959a04d7a434b63eef1ddded8c48dfa40fe5ad 🚀
2025-04-14 Deploying to gh-pages from @ Jonathan-0101/PenTestingDevice@a24afe124a70235f694ad3fb291c6f14e448afbd 🚀
2025-04-15 Jamming and recording / playback of raw data working
2025-04-15 Deploying to gh-pages from @ Jonathan-0101/PenTestingDevice@4c980a462a3bd212825694e72d96074b02dc04c4 🚀
2025-04-15 Added doxygen comments to SubGHzTools.h
2025-04-15 Deploying to gh-pages from @ Jonathan-0101/PenTestingDevice@e25ffce34339309b5bbf88d20c76ab083c91ff4a 🚀
2025-04-15 Remove README.md from WiFi and IR folders
2025-04-15 Deploying to gh-pages from @ Jonathan-0101/PenTestingDevice@7205517ec918a42f17cdcdf14342097a1b710aee 🚀
2025-04-15 Deploying to gh-pages from @ Jonathan-0101/PenTestingDevice@24a0e74700780b3f185bb54d213f41cfe2d16d88 🚀
2025-04-15 Deploying to gh-pages from @ Jonathan-0101/PenTestingDevice@ac9baf6cedcc80f3e8fc1ea4faae656d24157d08 🚀
2025-04-15 Update Doxyfile again
2025-04-15 Update Doxyfile again again
2025-04-15 Deploying to gh-pages from @ Jonathan-0101/PenTestingDevice@55beb1067d35a21ec8cd53dbb76ef7bbdf0840e6 🚀
2025-04-15 Updating comments
2025-04-15 Deploying to gh-pages from @ Jonathan-0101/PenTestingDevice@aabd2811f7f9ebc95aec5d42f9921dfd2abbbc83 🚀
2025-04-19 GUI fixes
2025-04-19 Deploying to gh-pages from @ Jonathan-0101/PenTestingDevice@f4538c5991c762d9c3992449624b64f855740964 🚀
2025-04-20 Deploying to gh-pages from @ Jonathan-0101/PenTestingDevice@397020f93bf31e7b62ff25d9846b25e1537118e6 🚀
2025-04-21 Deploying to gh-pages from @ Jonathan-0101/PenTestingDevice@1b83ec40f123e975ff7e89da2db0e7e0b1310bbb 🚀
2025-04-22 SPI instance acquisition added
2025-04-22 Deploying to gh-pages from @ Jonathan-0101/PenTestingDevice@4266719e6af250c015eacef62f0e3834fded4668 🚀
2025-04-25 SubGHz module updated
2025-04-25 Deploying to gh-pages from @ Jonathan-0101/PenTestingDevice@8a43a9f05c8900c46878c70c547cde626b761833 🚀
2025-04-30 Fix SD card initialisation in WiFiTools
2025-04-30 Deploying to gh-pages from @ Jonathan-0101/PenTestingDevice@fd65365e9b9cb33d0caff9cbc35d01aecc1c8d1b 🚀
2025-05-02 Housekeeping
2025-05-02 Deploying to gh-pages from @ Jonathan-0101/PenTestingDevice@54bf453e8c49c67909f39310652ae70e8928cd22 🚀
2025-05-05 Deploying to gh-pages from @ Jonathan-0101/PenTestingDevice@464e21257dc9f9a1ca5e3c05690f94b1e561858f 🚀
2025-05-05 Update LICENSE
2025-05-05 Deploying to gh-pages from @ Jonathan-0101/PenTestingDevice@ac9201835cb2c610074fb8e82309d9129afe4135 🚀
2025-05-06 Tidyup
2025-05-06 Deploying to gh-pages from @ Jonathan-0101/PenTestingDevice@1c43dbef5b1d8cc40dff3041e6a16269572adbfd 🚀
2025-05-06 Deploying to gh-pages from @ Jonathan-0101/skeletonKey@51966bd8ce107201f62e23201835bf07bffc5213 🚀
2025-05-06 Deploying to gh-pages from @ Jonathan-0101/skeletonKey@2a33793e0d4642f4f1e229cc55de90747f044c53 🚀
2025-05-07 Libraries added to GUI
2025-05-07 Deploying to gh-pages from @ Jonathan-0101/skeletonKey@de92746e03634fd9c524d3da82486a462660603b 🚀
2025-05-07 Update wifi
2025-05-07 Deploying to gh-pages from @ Jonathan-0101/skeletonKey@d62468b7d93a2e51279b5f6b1ba184d0b2ba4a38 🚀
2025-05-13 Added subGHz module initalisation error handeling
2025-05-13 Deploying to gh-pages from @ Jonathan-0101/skeletonKey@da42005ff8cf00a003d03a9be6db867790e1714c 🚀
2025-05-16 Deploying to gh-pages from @ Jonathan-0101/skeletonKey@36e618839eb49304a76953ef6a8e5a4d40048fb7 🚀
2025-05-16 Deploying to gh-pages from @ Jonathan-0101/skeletonKey@451ff1f1317d5a4a0fe188bafd2bc8b471258429 🚀
2025-05-16 Update cover image
2025-05-17 Deploying to gh-pages from @ Jonathan-0101/skeletonKey@84ed15f25df8ca118ff1bd7a73e0d3b6a632cb0d 🚀
2025-05-17 Deploying to gh-pages from @ Jonathan-0101/skeletonKey@a62f22ad59a38e8946735f0d4b772d5128fbe340 🚀
2025-05-20 Update HTML
2025-05-20 Deploying to gh-pages from @ Jonathan-0101/skeletonKey@f905970144cae77e401a97dd31e811dae1ed9408 🚀
2025-05-20 Update code
2025-05-20 Deploying to gh-pages from @ Jonathan-0101/skeletonKey@4c94f85ac16e9dffb3abfbff59eb7d0e42fbfda6 🚀
2025-05-20 Deploying to gh-pages from @ Jonathan-0101/skeletonKey@73ccdcee205139f32b4640e33f47f0eee460b8e5 🚀
2025-05-20 Add doxygen to ino files
2025-05-22 Deploying to gh-pages from @ Jonathan-0101/skeletonKey@657e2326bb6e7441ba74e14c841dbc130e0e53e8 🚀
2025-05-29 Update IR Menu page
2025-05-29 Deploying to gh-pages from @ Jonathan-0101/skeletonKey@408ef2c098e64c1af118d302c58dae2fb99f2cd6 🚀
2025-05-29 Add Doxyy header to GUI_GSLC.h
2025-05-29 Deploying to gh-pages from @ Jonathan-0101/skeletonKey@6f7aafe0c47119e0e54e09cad6cea9c810e7af78 🚀
2025-05-30 Deploying to gh-pages from @ Jonathan-0101/skeletonKey@002107d0acb531fd1490c6d1efa3adbdd0620210 🚀
2025-06-02 Update beacon spam to toggle
2025-06-02 Deploying to gh-pages from @ Jonathan-0101/skeletonKey@060bf0089a5412d1f66e8b2190680b7481826ee5 🚀
2025-07-08 Update readme and GUI
2025-07-08 Deploying to gh-pages from @ Jonathan-0101/skeletonKey@cf46e1a5da16558f5fbbe7bac0021eec4fa5eef0 🚀
2025-07-08 Deploying to gh-pages from @ Jonathan-0101/skeletonKey@ceb50369122401375dbfaa1468c3b254a13fdbd8 🚀
2025-07-19 Reorganisation
2025-07-19 Deploying to gh-pages from @ Jonathan-0101/skeletonKey@90d7ba4f93e78a3096ed0ebbfa44fa0c7b8eaca2 🚀
2025-07-19 Adding PCB files
2025-07-19 Deploying to gh-pages from @ Jonathan-0101/skeletonKey@1cd22f88ca35fbce9ac4a247e2b902d3eafcc058 🚀
2025-07-19 Update Hardware/Readme
2025-07-19 Deploying to gh-pages from @ Jonathan-0101/skeletonKey@e1a09e23fe2f73f4d980ad2c745759634318b2b3 🚀
2025-07-19 Deploying to gh-pages from @ Jonathan-0101/skeletonKey@89101b3ceac6bc6b011add403f970762b32a5ecb 🚀
2025-07-19 Deploying to gh-pages from @ Jonathan-0101/skeletonKey@1c57c08037f71f5ffb2df6be3034fde34b57bd05 🚀
2025-07-19 Deploying to gh-pages from @ Jonathan-0101/skeletonKey@511303d0319344c43e1eaff1aacacc72636ffbe5 🚀
2025-07-19 Update Doxygen header
2025-07-19 Deploying to gh-pages from @ Jonathan-0101/skeletonKey@bdea80aee4362201782916de6b0ef08d2ad0b3e7 🚀
2025-07-19 Update file associations
2025-12-04 Deploying to gh-pages from @ Jonathan-0101/skeletonKey@f2ee520d8953bbebee1f096209b67e0febb68e09 🚀
